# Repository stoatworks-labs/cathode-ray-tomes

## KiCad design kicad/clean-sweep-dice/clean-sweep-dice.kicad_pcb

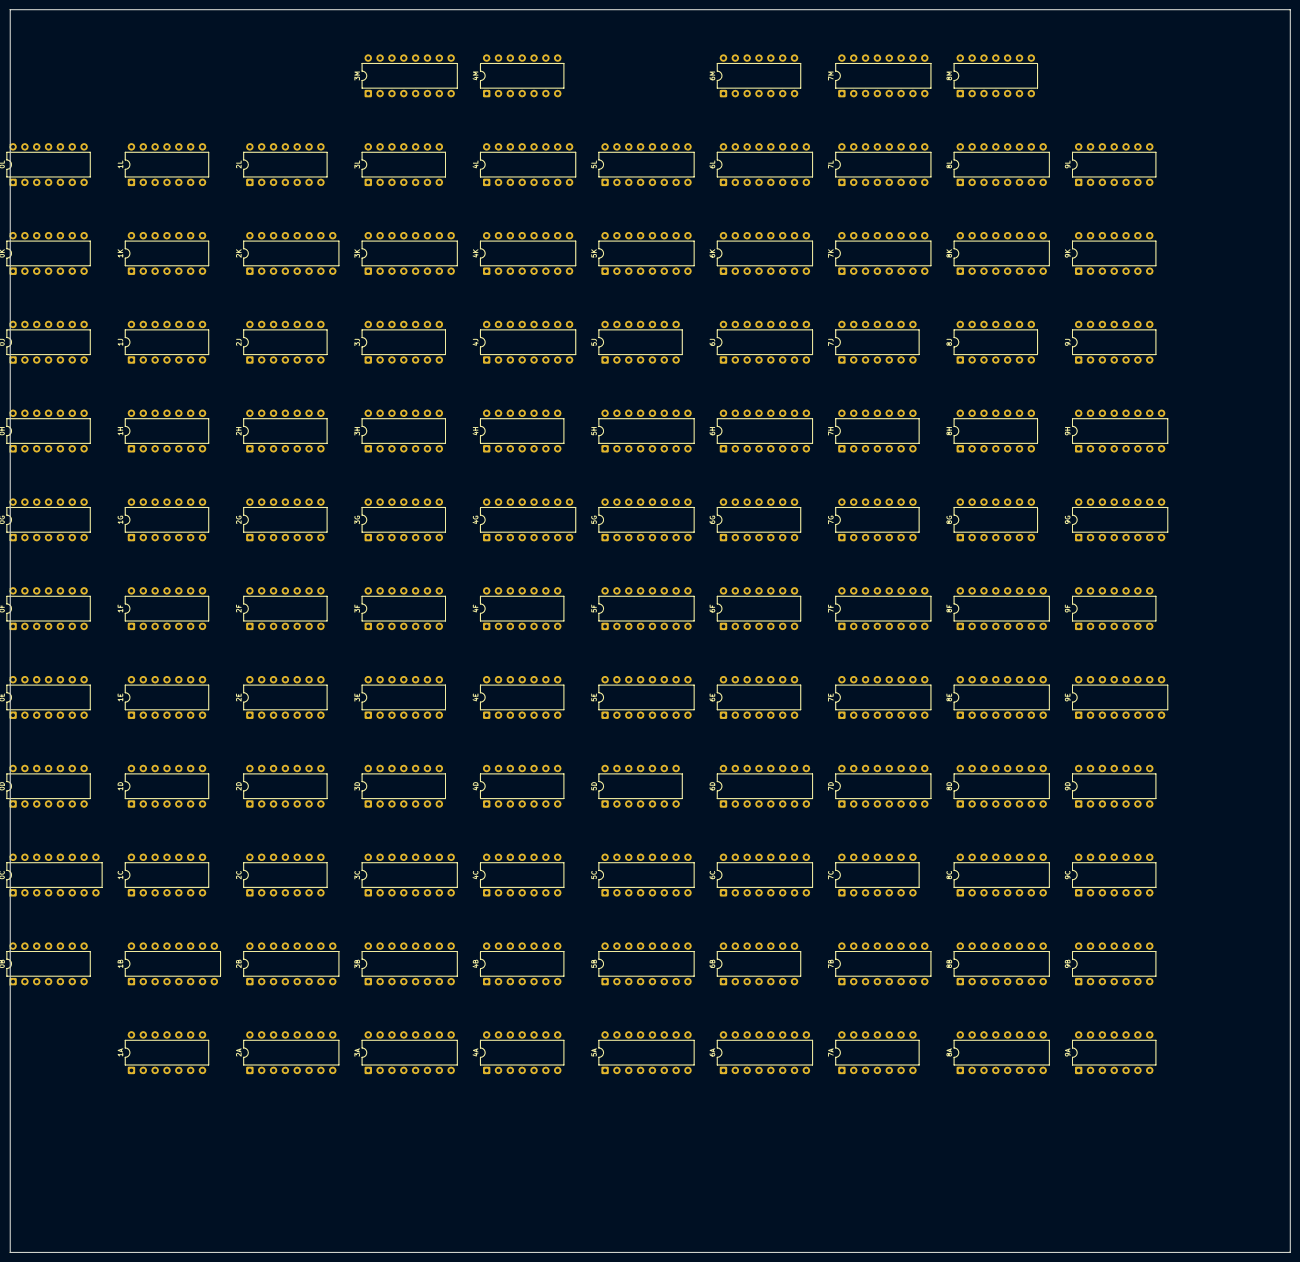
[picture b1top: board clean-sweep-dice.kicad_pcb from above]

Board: 2 copper layers, 274.6 x 266.6 mm, 114 parts (0 on the bottom side), 389 nets, no tracks yet.

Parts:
0B, 1F, 1K, 2D, 3D, 4B, 6G, 8M, 9A: 7404; DIP-14_W7.62mm
0C, 1B, 3A, 3M, 4J, 5A, 5E, 5G, 5H, 6H, 7F, 7M, 9E, 9H: 74S112; DIP-16_W7.62mm
0D, 0E, 0H, 1G, 1H, 4H, 6E, 6M, 8J, 9C, 9L: 7420; DIP-14_W7.62mm
0F, 1E, 2G, 3G, 3H, 4F, 6B, 7J: 7421; DIP-14_W7.62mm
0G, 2E, 3E, 7C: 7486; DIP-14_W7.62mm
0J, 1J, 4D: 7427; DIP-14_W7.62mm
0K, 2C, 2H, 2J, 3L, 4A, 4C, 5J, 7A, 8G, 9D, 9F, 9J: 7400; DIP-14_W7.62mm
0L, 1D, 2F, 2L, 5D, 7G, 8H: 7408; DIP-14_W7.62mm
1A, 1C: 7437; DIP-14_W7.62mm
1L, 3F, 3J, 4E, 4M, 6F, 7H, 9B, 9K: 7402; DIP-14_W7.62mm
2A, 2B, 3B, 3C, 4G, 6A, 6J, 6K, 6L, 7E, 7K, 7L, 8D, 8E, 8F, 8K, 8L, 9G: 74161; DIP-16_W7.62mm
2K: 74166; DIP-16_W7.62mm
3K, 6C, 7D: 82S123; DIP-16_W7.62mm
4K, 4L, 5K, 5L: 74151; DIP-16_W7.62mm
5B, 5C: 82S16; DIP-16_W7.62mm
5F: 74191; DIP-16_W7.62mm
6D: 74S151; DIP-16_W7.62mm
7B, 8C: 74174; DIP-16_W7.62mm
8A, 8B: 74S174; DIP-16_W7.62mm

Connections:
+5V: 0B.14, 0C.16, 0D.14, 0E.14, 0F.14, 0G.14, 0H.14, 0J.14, 0K.14, 0L.14, 1A.14, 1B.16, 1C.14, 1D.14, 1E.14, 1F.14, 1G.14, 1H.14, 1J.14, 1K.14, 1L.14, 2A.16, 2B.16, 2C.14, 2D.14, 2E.14, 2F.14, 2G.14, 2H.14, 2J.14, 2K.16, 2L.14, 3A.16, 3B.16, 3C.16, 3D.14, 3E.14, 3F.14, 3G.14, 3H.14, 3J.14, 3K.16, 3L.14, 3M.16, 4A.14, 4B.14, 4C.14, 4D.14, 4E.14, 4F.14, 4G.16, 4H.14, 4J.16, 4K.16, 4L.16, 4M.14, 5A.16, 5D.14, 5E.16, 5F.16, 5G.16, 5H.16, 5J.14, 5K.16, 5L.16, 6A.16, 6B.14, 6C.16, 6D.16, 6E.14, 6F.14, 6G.14, 6H.16, 6J.16, 6K.16, 6L.16, 6M.14, 7A.14, 7B.16, 7C.14, 7D.16, 7E.16, 7F.16, 7G.14, 7H.14, 7J.14, 7K.16, 7L.16, 7M.16, 8A.16, 8B.16, 8C.16, 8D.16, 8E.16, 8F.16, 8G.14, 8H.14, 8J.14, 8K.16, 8L.16, 8M.14, 9A.14, 9B.14, 9C.14, 9D.14, 9E.16, 9F.14, 9G.16, 9H.16, 9J.14, 9K.14, 9L.14
GND: 0B.7, 0C.8, 0D.7, 0E.7, 0F.7, 0G.7, 0H.7, 0J.7, 0K.7, 0L.7, 1A.7, 1B.8, 1C.7, 1D.7, 1E.7, 1F.7, 1G.7, 1H.7, 1J.7, 1K.7, 1L.7, 2A.4, 2A.8, 2B.5, 2B.8, 2C.7, 2D.7, 2E.7, 2F.7, 2G.7, 2H.7, 2J.7, 2K.1, 2K.2, 2K.6, 2K.8, 2K.14, 2L.7, 3A.8, 3B.3, 3B.4, 3B.6, 3B.8, 3C.3, 3C.8, 3D.7, 3E.7, 3F.7, 3G.7, 3H.7, 3J.7, 3K.8, 3K.15, 3L.7, 3M.8, 3M.11, 4A.7, 4B.7, 4C.7, 4D.7, 4E.7, 4F.7, 4G.3, 4G.4, 4G.5, 4G.6, 4G.8, 4H.7, 4J.8, 4K.8, 4L.8, 4M.7, 5A.8, 5D.7, 5E.8, 5E.12, 5F.1, 5F.8, 5F.9, 5F.10, 5F.15, 5G.8, 5H.8, 5J.7, 5K.8, 5L.8, 6A.3, 6A.4, 6A.5, 6A.6, 6A.8, 6B.7, 6C.8, 6C.15, 6D.8, 6E.7, 6F.6, 6F.7, 6G.7, 6H.8, 6J.4, 6J.5, 6J.6, 6J.8, 6K.3, 6K.4, 6K.5, 6K.6, 6K.8, 6L.3, 6L.4, 6L.5, 6L.6, 6L.8, 6M.7, 7A.7, 7B.8, 7B.13, 7B.14, 7C.7, 7D.8, 7D.15, 7E.8, 7F.8, 7G.7, 7H.7, 7J.7, 7K.3, 7K.4, 7K.5, 7K.6, 7K.8, 7L.3, 7L.4, 7L.5, 7L.6, 7L.8, 7M.2, 7M.8, 8A.8, 8B.8, 8C.8, 8D.8, 8E.3, 8E.5, 8E.6, 8E.8, 8F.3, 8F.4, 8F.5, 8F.8, 8G.7, 8H.7, 8J.7, 8K.3, 8K.4, 8K.5, 8K.6, 8K.8, 8L.3, 8L.4, 8L.5, 8L.6, 8L.8, 8M.7, 9A.7, 9B.7, 9C.7, 9D.7, 9E.8, 9E.12, 9F.7, 9G.3, 9G.4, 9G.5, 9G.6, 9G.8, 9H.8, 9J.7, 9K.7, 9L.7
VCC: 0C.4, 0C.10, 0C.14, 0C.15, 0G.13, 1B.2, 1B.3, 1B.4, 1B.10, 1B.15, 2A.1, 2A.6, 2A.7, 2A.10, 2B.1, 3A.4, 3A.10, 3A.14, 3A.15, 3B.1, 3B.7, 3B.10, 3C.1, 3M.4, 3M.14, 4G.9, 4J.4, 4J.10, 5A.4, 5A.10, 5A.14, 5A.15, 5E.4, 5E.10, 5G.14, 5G.15, 5H.4, 5H.15, 6A.7, 6A.9, 6H.4, 6H.10, 6J.3, 6K.7, 6K.10, 6L.7, 6L.10, 7B.11, 7F.10, 7K.7, 7K.10, 7L.7, 7L.10, 7M.10, 7M.14, 8A.1, 8B.1, 8C.1, 8C.14, 8E.1, 8E.4, 8F.1, 8F.6, 8K.7, 8K.10, 8L.7, 8L.10, 9G.9, 9H.4, 9H.10
_1BLGE: 7A.13, 9A.6
_1BVCF: 0F.4, 1L.3, 4F.1, 4F.2, 7G.2, 7G.10, 8G.1, 9A.8
_1GBCC: 0L.2, 4B.6
_1KBAR: 4J.11, 7B.9, 8B.10, 9E.1, 9F.13
_1KBAS: 5H.11, 6G.4
_1N25C: 6G.8, 9H.11
_1PERA: 4E.12, 4J.3, 5G.11, 8B.7
_1PGOT: 0F.5, 3D.12
_1PVBL: 0K.8, 6E.4
_1RRLM: 1F.12, 7A.1
_1RVID: 6G.2, 7G.5
_1SEDA: 6F.9, 7M.11, 9A.12
_1TBCF: 1L.6, 8M.12
_1TEC4: 2D.8, 4K.10, 4L.10, 5B.2, 5C.2, 5K.10, 5L.10
_1TEC5: 0E.10, 1E.10, 2D.10, 5B.1, 5C.1
_1TECC: 0B.10, 3A.2, 3A.3
_1TEG7: 0B.12, 1D.5, 4K.9, 4L.9, 5K.9, 5L.9, 9D.1
_1TLCC: 0L.5, 2L.2, 3A.11, 3A.12, 4B.4, 4G.7, 7F.1, 9F.4, 9G.7, 9G.10
_1TQ05: 1A.9, 1A.10, 1B.5
_1TQ10: 1A.1, 1A.2, 1B.1
_2THSC: 1C.6, 3A.13, 9H.1
_2TQ05: 0C.1, 0C.13, 1A.11, 1B.13, 3A.1, 5A.1, 9H.13
_2TQ10: 1A.6, 4J.13, 5E.1, 5G.13, 5H.13, 7F.13
_3XBL5: 1K.8, 4M.8
_5AERD: 1H.8, 1J.9
_5AERE: 1H.6, 1J.13
_5AFNE: 0J.8, 1J.10
_5AFNF: 0J.12, 1J.2
_5AGOT: 3J.10, 3J.12
_5ALVD: 1L.10, 9L.2
_5ARBK: 1J.11, 2J.6
_5ASBK: 1J.1, 2J.8
_5BELD: 7A.11, 7E.9
_5BL35: 4M.4, 8J.4
_5BL57: 8J.2, 9A.10
_5BLCB: 8C.3, 9A.4
_5BLGA: 8C.2, 8C.4, 9C.5, 9D.9
_5BLGB: 8C.5, 8C.6, 9C.4
_5BLGC: 8C.7, 8C.11, 9C.2
_5BLGD: 8C.10, 8C.13, 9C.1, 9D.10
_5BLGE: 8C.12, 8D.9, 9A.5
_5BOPD: 5H.10, 8G.6
_5BSCL: 7C.4, 7C.10, 7C.13, 7D.13, 9E.6
_5BSUP: 7D.14, 9E.7
_5BVAA: 9B.1, 9C.9, 9D.5
_5BVAB: 9B.4, 9C.10
_5BVAC: 9B.10, 9C.12
_5BVAD: 9B.13, 9C.13, 9D.4
_5BVCF: 6F.12, 6M.8, 9A.9
_5CNPA: 2H.6, 2H.13
_5CONA: 7H.5, 9H.7
_5CONR: 1E.5, 4C.6
_5CPLY: 8H.1, 8M.2
_5CRBK: 0H.6, 3H.10
_5CREA: 7H.1, 7H.6
_5CREU: 3M.6, 4C.1, 5G.4, 6B.12, 6B.13, 6H.13, 6J.9, 6K.1, 6L.1, 7K.1, 7L.1, 8K.1, 8L.1
_5CREW: 3M.2, 6G.10, 9H.14
_5CVID: 0K.3, 8B.14
_5DNBA: 1G.6, 3F.5
_5EBEA: 4H.9, 5J.3
_5EBEB: 4H.10, 5J.6
_5EBEC: 4H.12, 5J.8
_5EBED: 4H.13, 5J.11
_5EBEL: 4H.2, 4J.6
_5EBOP: 4H.4, 5H.7
_5EBUZ: 4H.5, 4J.14, 5H.6
_5EHIT: 4H.1, 4J.7, 6B.5
_5ENDA: 0H.5, 0L.10, 4C.13, 6F.2, 6H.6, 6H.12, 9F.9
_5ENDC: 6G.12, 6H.14
_5ESCL: 6F.1, 7B.1
_5GANC: 4C.2, 5G.10, 7M.7
_5GBCA: 1G.8, 2H.12
_5GBCC: 0J.6, 4B.5
_5GNCA: 1H.1, 2F.5, 2H.3
_5GNCC: 3F.13, 4K.7, 4L.7, 5K.7, 5L.7
_5HITA: 6B.6, 6D.7
_5KBAS: 6G.3, 8G.3, 9E.14
_5LODD: 0H.8, 2K.15
_5N25C: 1K.2, 6G.9, 9G.1, 9H.15
_5NABA: 1J.6, 6J.2, 7H.8
_5NCA3: 3L.10, 3L.13, 4B.12
_5NCHA: 0F.10, 3L.6, 4F.10
_5NCHB: 0F.12, 0F.13, 3L.8
_5NCHC: 3L.11, 4F.12, 4F.13
_5NGTB: 3F.1, 3F.8
_5NGTC: 3J.11, 4B.8
_5PGOT: 0D.8, 3D.13, 9L.4
_5PHLB: 9D.3, 9E.4
_5PHRC: 9E.15, 9F.3
_5PONE: 2J.10, 4E.6, 5G.6, 7J.1, 7J.2, 8G.13
_5PONF: 4E.1, 5B.3, 5B.4, 5B.5
_5PONG: 4E.4, 5C.3, 5C.4, 5C.5
_5PVBL: 0D.13, 0E.6, 0K.9, 0K.10
_5PVBU: 0D.6, 0D.12, 3F.9
_5RHCL: 7A.10, 7B.10
_5RHD1: 7A.9, 7B.2
_5RLA0: 5E.6, 6A.2
_5RLA1: 0K.11, 7B.3
_5RLA4: 0G.11, 9E.3
_5RRLA: 0E.8, 5D.5
_5RRLB: 4C.11, 5D.4
_5RRLM: 1F.13, 5D.6, 7M.4
_5RRST: 7A.3, 7A.5
_5RTEA: 4E.13, 5B.12, 5C.12
_5RVID: 6E.6, 6G.1, 9L.1
_5SBAA: 7L.2, 8L.9, 9J.6
_5SBBB: 6L.2, 7L.9, 9J.11
_5SBCC: 3L.3, 6L.9
_5SBDA: 9K.9, 9L.8
_5SBDB: 9K.1, 9K.8
_5SCAA: 7K.2, 8K.9, 9J.3
_5SCBB: 6K.2, 7K.9, 9J.8
_5SCCC: 2J.11, 6K.9
_5SCDA: 8J.8, 9K.5
_5SCDB: 7H.13, 9K.6
_5SCOA: 8G.8, 8K.2
_5SCOB: 8G.11, 8L.2
_5SEDA: 4M.3, 9A.13, 9K.13
_5SUBK: 2J.3, 2J.4, 2J.9
_5SURV: 7E.1, 7F.6, 7F.14, 8D.1, 8E.9, 8F.9
_5SURZ: 6F.4, 7F.4
_5TBCF: 1L.1, 8M.13
_5TEC0: 0H.9, 3D.6
_5TEC1: 0H.10, 3D.4
_5TEC2: 0H.12, 0H.13, 2D.2, 2G.9, 3G.2
_5TEC3: 1G.5, 1G.13, 2D.4, 2G.4, 3G.4
_5TEC4: 1G.12, 2D.6, 2D.9, 2H.9, 3G.9
_5TEC5: 1B.11, 1G.10, 1H.5, 2D.11, 3H.2, 4B.2
_5TEC6: 1H.4, 2D.12, 2H.5
_5TEC7: 1D.10, 1H.10, 3D.2
_5TEC8: 1D.4, 2A.3, 2A.5, 2B.3, 2B.4, 2B.6, 3A.6, 7A.2
_5TECC: 0B.11, 2A.9, 2B.9, 2C.3
_5TECD: 2C.6, 2C.9, 2C.13
_5TEG7: 0B.13, 2C.11, 9F.1
_5TEG8: 2C.8, 8B.13
_5THBL: 1F.10, 5E.14, 5E.15, 6A.1, 7M.15
_5THSC: 1B.7, 4A.12
_5TL01: 1C.11, 6B.1, 6B.2
_5TL48: 1C.8, 3M.10
_5TLBG: 1L.4, 9L.5
_5TLC1: 2G.1, 3D.8, 3G.1, 3K.10
_5TLC2: 2F.13, 3D.10, 3K.11
_5TLC4: 0D.5, 1F.2
_5TLC5: 0D.4, 1F.4
_5TLC6: 0D.2, 1F.6
_5TLC7: 0D.1, 1F.8
_5TLC8: 3A.7, 3C.4, 3C.5, 3C.6, 3J.3, 4G.10, 9F.5
_5TLCC: 3B.9, 3C.9, 4A.3, 4B.3
_5TLCD: 4A.6, 4A.9
_5TLG8: 4A.8, 8D.7, 8D.10
_5TLNC: 0C.6, 0C.12, 1D.13
_5TLND: 0C.7, 1D.12
_5TPWR: 3M.15, 5F.11, 6H.15, 6J.1, 8C.15
_5TVBL: 3J.1, 3J.5
_5TVSC: 4A.13, 4C.8, 5A.13
_5TWOP: 6H.7, 7J.10
_5UPAA: 7G.11, 9E.10
_5UPDN: 5F.5, 6F.10
_5UPEA: 6F.11, 9F.6
_5UPEC: 7G.12, 9F.8
_5UPGA: 7G.13, 9F.11
_5WRTA: 5A.7, 5B.13, 5C.13
_5ZERO: 0H.1, 0H.2, 2L.5, 6G.6
_6TEG8: 7E.7, 7E.10, 8B.12
_6THSC: 1C.3, 1C.4, 1C.5, 3B.2, 3C.2, 3M.13, 4G.2, 8C.9, 8D.2, 8E.2, 9G.2
_6TQ05: 1A.8, 1A.12, 1A.13, 2A.2, 2B.2, 2K.7, 7M.1, 9E.13
_6TQ10: 1A.3, 1A.4, 1A.5, 4J.1, 5H.1, 7E.2, 8A.9, 8B.9, 8F.2
_7ENDA: 6J.7, 6J.10, 7H.9, 8J.6
_9XBL5: 1K.9, 1L.12
_9XPLY: 8H.4, 8M.1
_ACLN: 0J.9, 0J.13, 2F.11
_AERA: 0G.3, 2F.10
_AERB: 2F.9, 2H.8
_AERC: 1H.12, 1H.13, 2F.8
_AFNA: 0J.10, 2G.6
_AFNB: 0J.11, 2G.8
_AFNC: 0J.2, 3G.6
_AFND: 0J.1, 3G.8
_AFNG: 1J.8, 3J.9
_AFNH: 1J.12, 3J.8
_AROT: 1L.9, 3J.13
_BEBB: 5D.11, 8F.7, 8F.10
_BECA: 5D.13, 7E.15, 7F.11, 7F.12
_BECB: 5D.12, 7F.9
_BECC: 8A.3, 8F.15
_BEGA: 8A.2, 8A.4, 9B.2
_BEGB: 8A.5, 8A.6, 9B.3
_BEGC: 8A.7, 8A.11, 9B.5
_BEGD: 8A.10, 8A.13, 9B.6
_BEGE: 8A.12, 8A.14, 9B.9
_BEGF: 8A.15, 8B.3, 9B.8
_BEGG: 8B.2, 8B.4, 9B.12
_BEGH: 7A.12, 8B.5, 9B.11
_BL35: 4M.5, 4M.6, 4M.10
_BL57: 1L.13, 9A.11
_BLCA: 8D.15, 8E.7, 8E.10
_BLCB: 8E.15, 9A.3
_BPE0: 7D.5, 7E.3
_BPE1: 7D.6, 7E.4
_BPE2: 7D.7, 7E.5
_BPE3: 7D.9, 7E.6
_BPL0: 7D.1, 8D.3
_BPL1: 7D.2, 8D.4
_BPL2: 7D.3, 8D.5
_BPL3: 7D.4, 8D.6
_BUZZ: 4F.6, 5H.3
_BVBA: 6M.9, 9C.8
_BVCA: 9D.6, 9D.12
_BVCB: 9D.8, 9D.13
_BVCD: 6M.10, 9D.11
_BVCE: 6M.12, 6M.13, 9C.6
_COBL: 0K.2, 3J.4
_CONA: 6F.8, 9H.9
_CRA0: 5F.3, 5K.12, 6B.10
_CRA1: 5F.2, 5L.12
_CRA2: 4K.12, 5F.6
_CRA3: 4L.12, 5F.7, 6B.9
_CRE1: 7H.3, 8H.6
_CRE2: 7H.2, 8H.3
_CREB: 4D.1, 7H.4
_CREC: 4D.12, 5F.14
_CREU: 1J.3, 3M.5, 4D.13, 5D.1, 6F.5, 6H.3
_CREW: 2L.6, 3M.3, 6G.11
_DNBB: 0G.5, 0J.3, 3F.4
_EBAA: 4G.1, 4H.6
_EBC1: 4G.13, 4J.2
_EBC2: 4G.12, 4J.12, 5H.12
_EBC3: 4G.11, 5G.1, 7J.5, 7J.9, 8J.1
_EBCC: 4G.15, 5H.2
_EBEE: 4H.8, 8H.12
_EBEL: 4J.5, 5J.9
_EBOP: 5H.9, 5J.5
_EBUZ: 5H.5, 5J.2, 7F.3
_EFEE: 4D.2, 4M.1
_EHIT: 4J.9, 5J.12
_ENDA: 0F.1, 0F.2, 0G.10, 4J.15, 5G.3, 5H.14, 6H.5, 6H.11, 7A.4, 7F.15, 8G.4, 8H.13, 9F.12
_ENDB: 0L.9, 6H.2, 7H.10
_ENDC: 0L.8, 6G.13
_ENDD: 0G.8, 7G.4
_FLA3: 0H.4, 2J.1, 8H.2, 9G.11
_FLAA: 3M.1, 8H.9, 9G.15, 9H.2, 9H.3
_FLAB: 0K.5, 8H.5, 8H.10, 9H.5
_FLAC: 8H.8, 9H.12
_FNCA: 3H.6, 3H.9
_FNCB: 0J.4, 3F.12, 3H.8
_GANC: 7M.9, 7M.12
_GBCB: 0J.5, 2H.11
_GNCB: 2F.6, 3F.11
_ILSB: 0G.6, 4K.11, 4L.11, 5K.11, 5L.11
_KBAL: 7G.3, 8G.5, 9D.2, 9F.2
_KBAR: 7G.8, 8B.11
_LIMT: 5F.4, 6B.8
_NACL: 1J.5, 7J.8
_NACM: 1J.4, 7J.6
_NBA0: 5K.1, 6J.14, 8J.5
_NBA1: 4M.9, 5L.1, 6J.13
_NBA2: 1L.11, 4K.1, 6J.12
_NBA3: 4L.1, 6J.11
_NCA0: 3K.12, 5K.5
_NCA1: 3K.13, 5L.5
_NCA2: 3K.14, 4K.5
_NCA3: 4B.13, 4L.5
_NCG2: 3K.3, 3L.12
_NCG3: 3K.4, 3L.9
_NCG4: 3K.5, 3L.5
_NCG5: 2K.3, 2K.4, 3K.6
_NCG6: 3K.7, 4F.9
_NCG7: 0F.9, 3K.9
_NCH6: 2K.5, 2K.10, 4F.8
_NCH7: 0F.8, 2K.11, 2K.12
_NCIV: 0L.1, 2K.13
_NCOT: 0L.3, 1L.5
_NGTA: 2F.3, 2G.13, 2L.9, 3F.2, 3G.13, 3M.12
_NGTC: 2K.9, 3F.10, 4B.9
_NLC3: 2L.8, 3L.4
_PERA: 0F.6, 8B.6
_PGHT: 1D.2, 2E.8
_PGTA: 1D.3, 1E.4
_PGTB: 1E.1, 1E.2, 4E.10
_PGTC: 0D.9, 1E.6
_PHGU: 3E.6, 4E.9
_PONE: 2J.5, 4E.3, 5G.5, 7J.12, 7J.13, 8G.10
_PVGT: 1D.1, 3E.3
_PVGU: 3E.8, 4E.8
_RAT0: 6C.1, 6D.4
_RAT1: 6C.2, 6D.3
_RAT2: 6C.3, 6D.2
_RAT3: 6C.4, 6D.1
_RAT4: 6C.5, 6D.15
_RAT5: 6C.6, 6D.14
_RAT6: 6C.7, 6D.13
_RAT7: 6C.9, 6D.12
_RBLA: 5E.11, 6A.15
_RBLB: 5E.9, 7C.1
_RESA: 4C.3, 5A.3
_RGTE: 6A.10, 6E.5, 7C.3
_RH12: 7A.8, 7C.5
_RHD2: 7B.5, 7C.9
_RHD3: 7B.7, 7C.12
_RL34: 3E.11, 6B.4
_RLA0: 5E.5, 5E.13, 6C.10
_RLA1: 0K.12, 0K.13, 6A.14, 6C.11
_RLA2: 6A.13, 6C.12, 7B.4
_RLA3: 3E.12, 6A.12, 6C.13, 7B.6
_RLA4: 0G.12, 3E.13, 6A.11, 6C.14, 9E.2
_RLAA: 5E.2, 5E.3, 7C.2, 7M.5
_RSP1: 7C.6, 7D.10
_RSP2: 7C.8, 7D.11
_RSP3: 7C.11, 7D.12
_RVIA: 6D.6, 6E.1
_RVIC: 7G.6, 7G.9
_SBA0: 5K.13, 8L.14, 9J.5
_SBA1: 5L.13, 8L.13, 9L.9
_SBA2: 4K.13, 8L.12, 9L.10
_SBA3: 4L.13, 8L.11, 9J.4
_SBB0: 5K.14, 7L.14, 9J.12, 9L.12
_SBB1: 5L.14, 7L.13
_SBB2: 4K.14, 7L.12
_SBB3: 4L.14, 7L.11, 9J.13, 9L.13
_SBC0: 3L.2, 5K.15, 6L.14, 9K.2
_SBC1: 5L.15, 6L.13, 9K.3
_SBC2: 4K.15, 6L.12
_SBC3: 3L.1, 4L.15, 6L.11
_SBDC: 9K.10, 9K.11
_SCA0: 5K.2, 8K.14, 9J.2
_SCA1: 5L.2, 8J.9, 8K.13
_SCA2: 4K.2, 8J.10, 8K.12
_SCA3: 4L.2, 8K.11, 9J.1
_SCB0: 5K.3, 7K.14, 8J.12, 9J.9
_SCB1: 5L.3, 7K.13
_SCB2: 4K.3, 7K.12
_SCB3: 4L.3, 7K.11, 8J.13, 9J.10
_SCC0: 2J.12, 5K.4, 6K.14, 7H.12
_SCC1: 5L.4, 6K.13, 7H.11
_SCC2: 4K.4, 6K.12
_SCC3: 2J.13, 4L.4, 6K.11
_SCDC: 9K.4, 9K.12
_SCOR: 5G.9, 8G.9, 8G.12
_SURR: 2L.3, 7F.2
_SURV: 0K.4, 2J.2, 6F.3, 7F.5, 9E.11
_TCSA: 4C.9, 4D.6
_TCSC: 1K.5, 4A.11, 4F.5
_TE10: 2E.3, 4C.5
_TE78: 0E.13, 1D.6, 4C.12
_TEC0: 0E.9, 2A.14, 2E.2, 3D.5
_TEC1: 2A.13, 2E.1, 3D.3, 3E.4
_TEC2: 2A.12, 2D.1, 2E.9, 2G.5, 3E.5, 3G.12
_TEC3: 0G.4, 2A.11, 2B.10, 2D.3, 2E.10, 2G.10, 2H.2, 2H.10, 3G.10, 3H.5
_TEC4: 0G.2, 1E.9, 1G.4, 2B.14, 2D.5, 2G.2, 2G.12, 2H.1, 3G.5, 3H.4
_TEC5: 0G.1, 1B.12, 1G.2, 2B.13, 2F.4, 2H.4, 4B.1
_TEC6: 0E.12, 1E.12, 1G.1, 1G.9, 1H.9, 2B.12, 2D.13, 3H.1, 5B.15, 5C.15
_TEC7: 1E.13, 1H.2, 2B.11, 2C.12, 3D.1, 3F.6, 3H.12, 3H.13, 5B.14, 5C.14
_TEC8: 1B.14, 2C.4, 2C.10, 3A.5
_TECA: 1D.9, 2A.15, 2B.7, 2C.1
_TECB: 2B.15, 2C.2, 2C.5
_THBL: 1D.11, 1F.11, 3J.6
_THSC: 1B.9, 1C.1, 1C.2
_TL01: 1C.12, 1C.13, 4D.8
_TL10: 2E.6, 4C.4
_TL32: 0L.11, 3C.10
_TL48: 1C.9, 1C.10, 5D.8
_TL49: 3M.9, 8G.2
_TLC0: 2E.5, 3B.14, 4D.9, 6D.11
_TLC1: 2E.4, 2F.2, 2F.12, 3B.13, 3D.9, 3E.10, 4D.10, 6D.10
_TLC2: 0L.12, 2F.1, 3B.12, 3D.11, 3E.2, 3E.9, 4D.3, 4D.11, 5J.10, 6D.9
_TLC3: 0L.13, 2L.10, 3B.11, 3E.1, 3F.3, 4D.4, 5J.13, 6E.2
_TLC4: 0E.5, 1F.1, 3C.14, 4D.5, 5B.7, 5C.7, 5D.9, 5J.4
_TLC5: 0E.4, 1F.3, 3C.13, 5B.9, 5C.9
_TLC6: 0E.2, 1F.5, 3C.12, 5B.10, 5C.10, 5J.1
_TLC7: 0E.1, 1F.9, 3C.11, 5B.11, 5C.11
_TLC8: 0G.9, 0L.4, 3A.9, 3B.5, 4A.4, 4A.10, 4C.10, 4F.4, 5D.10, 5G.12, 6H.1, 7M.13
_TLCA: 3B.15, 3C.7, 4A.1
_TLCB: 3C.15, 4A.2, 4A.5
_TLGV: 0L.6, 1L.2, 3J.2
_TLHB: 0C.2, 1E.8
_TLNA: 0C.3, 1D.8
_TLNC: 0C.5, 0C.11, 2E.12
_TLND: 0C.9, 2E.13
_TLNE: 1L.8, 2E.11, 7G.1
_TWOP: 5G.2, 6H.9, 7J.4
_UPEB: 6F.13, 9F.10
_VIDA: 0K.1, 9L.6
_WRTA: 4E.11, 5A.2, 5A.9, 5A.12, 5D.2
_WRTB: 4E.2, 4E.5, 5D.3
_WRTZ: 5A.5, 5A.11
_ZERO: 5F.12, 6G.5

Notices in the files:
kicad/clean-sweep-dice/cleansweep.cpp:
COPYRIGHT 1974 MADE IN USA
